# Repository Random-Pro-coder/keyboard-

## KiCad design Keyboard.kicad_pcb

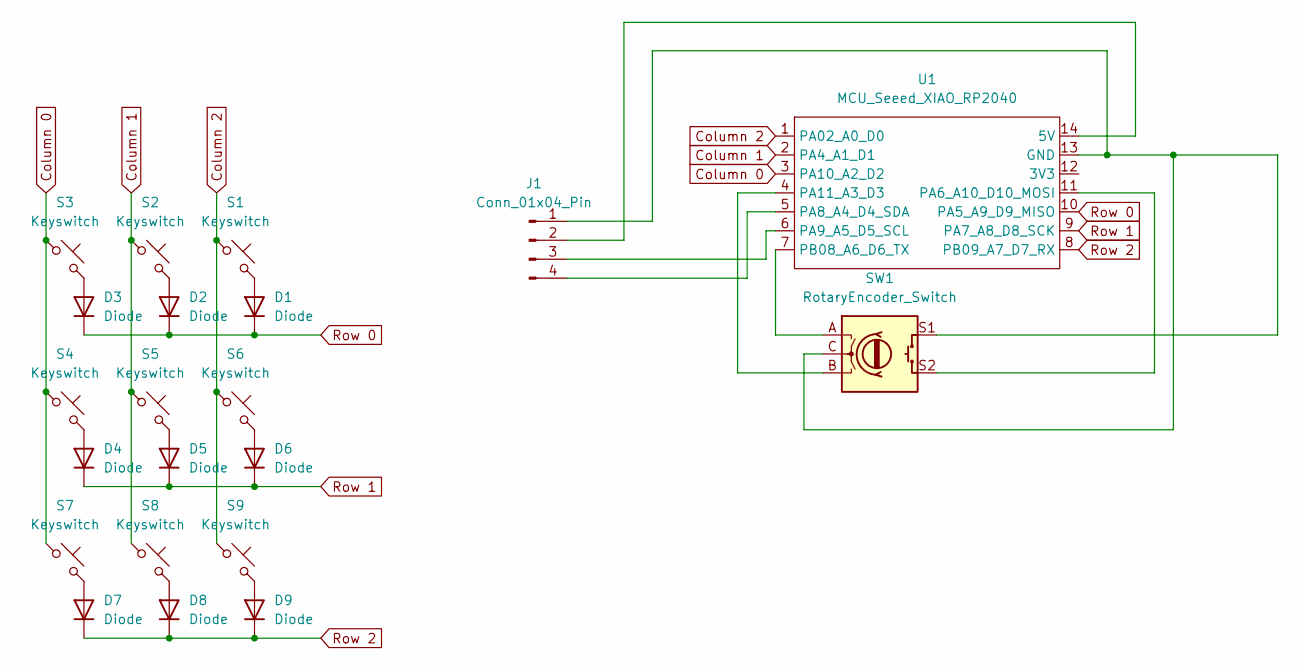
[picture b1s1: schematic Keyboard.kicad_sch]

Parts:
D1, D2, D3, D4, D5, D6, D7, D8, D9: Diode; Diode_DO-35
J1: Conn_01x04_Pin; PinHeader_1x04_P2.54mm_Vertical
S1, S2, S3, S4, S5, S6, S7, S8, S9: Keyswitch; SW_Cherry_MX_1.00u_PCB
SW1: RotaryEncoder_Switch; RotaryEncoder_Alps_EC11E-Switch_Vertical_H20mm
U1: MCU_Seeed_XIAO_RP2040; XIAO-Generic-Thruhole-14P-2.54-21X17.8MM

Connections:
Column 0: S3.1, S4.1, S7.1, U1.3 (PA10_A2_D2)
Column 1: S2.1, S5.1, S8.1, U1.2 (PA4_A1_D1)
Column 2: S1.1, S6.1, S9.1, U1.1 (PA02_A0_D0)
unnamed: D1.2 (A), S1.2
unnamed: D2.2 (A), S2.2
unnamed: D3.2 (A), S3.2
unnamed: D4.2 (A), S4.2
unnamed: D5.2 (A), S5.2
unnamed: D6.2 (A), S6.2
unnamed: D7.2 (A), S7.2
unnamed: D8.2 (A), S8.2
unnamed: D9.2 (A), S9.2
unnamed: J1.1, SW1.C, SW1.S1, U1.13 (GND)
unnamed: J1.2, U1.14 (5V)
unnamed: J1.3, U1.6 (PA9_A5_D5_SCL)
unnamed: J1.4, U1.5 (PA8_A4_D4_SDA)
unnamed: SW1.S2, U1.11 (PA6_A10_D10_MOSI)
unnamed: SW1.B, U1.4 (PA11_A3_D3)
unnamed: SW1.A, U1.7 (PB08_A6_D6_TX)
Row 0: D1.1 (K), D2.1 (K), D3.1 (K), U1.10 (PA5_A9_D9_MISO)
Row 1: D4.1 (K), D5.1 (K), D6.1 (K), U1.9 (PA7_A8_D8_SCK)
Row 2: D7.1 (K), D8.1 (K), D9.1 (K), U1.8 (PB09_A7_D7_RX)

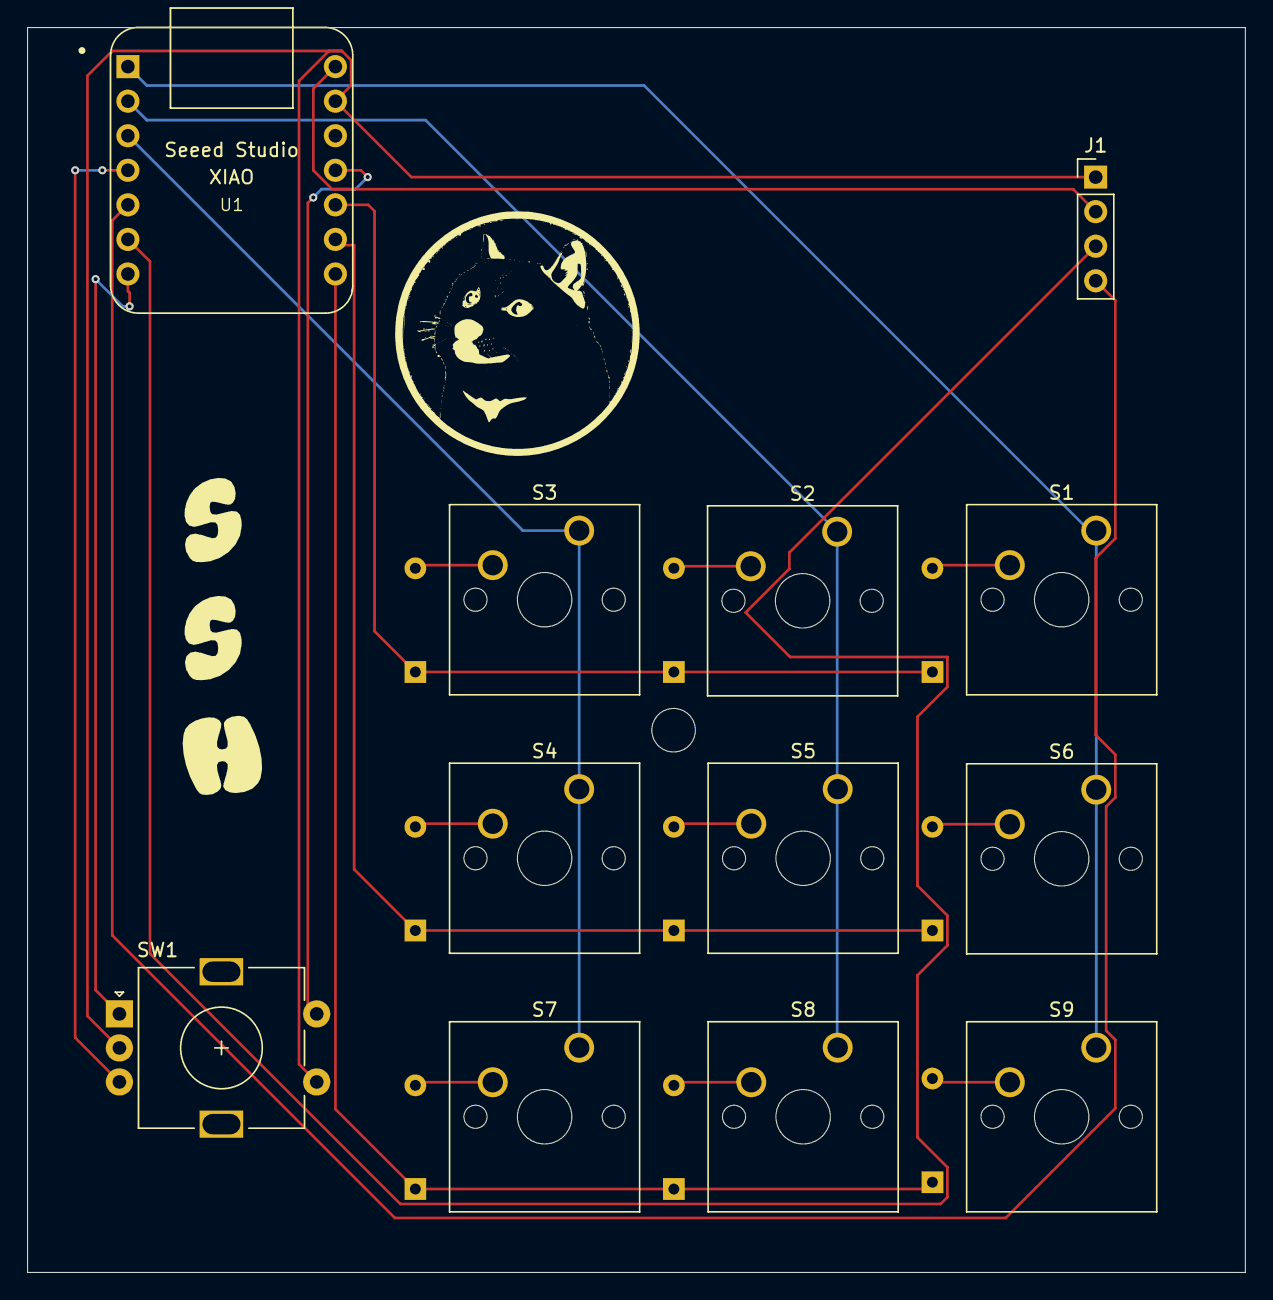
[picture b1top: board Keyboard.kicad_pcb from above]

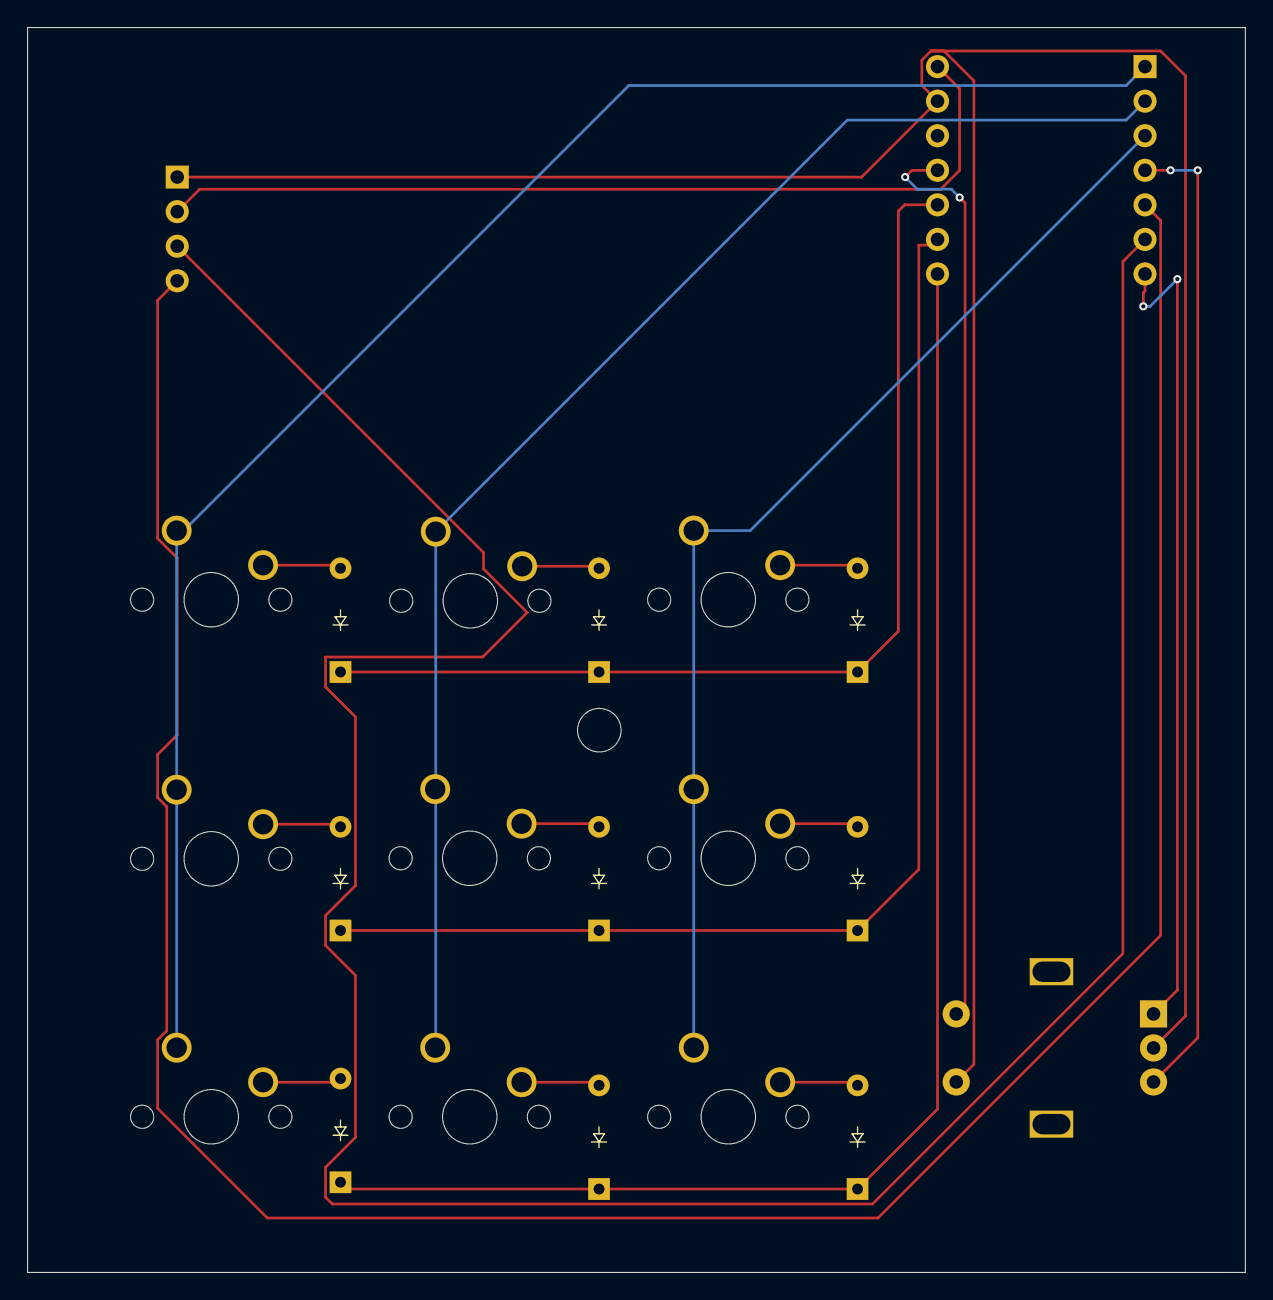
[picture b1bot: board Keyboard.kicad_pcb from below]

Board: 2 copper layers, 89.5 x 91.5 mm, 21 parts (9 on the bottom side), 22 nets.

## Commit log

2024-10-02 added libraries
